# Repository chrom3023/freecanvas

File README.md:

# freecanvas #

         ___             ___                      
        | __| _ ___ ___ / __|__ _ _ ___ ____ _ ___
        | _| '_/ -_) -_) (__/ _` | ' \ V / _` (_-<
        |_||_| \___\___|\___\__,_|_||_\_/\__,_/__/

FreeCanvas is a development environment for experimental art based on Arduino.

## ChangeLog ##

-   FreeCanvas usa [versionamiento semántico](http://semver.org).  
-   Fuente de alimentación implementada.  
-   Fuente con salidas independientes.  
-   Actualizado el procesador a *ATMEGA2560*.  
-   Conexión USB a través de *FT232*.  
-   Incorporado conector AVRISP de seis pines.  
-   Añadidos múltiples indicadores de estado.  
-   Añadida la posibilidad de conectar varios maestros en cascada.

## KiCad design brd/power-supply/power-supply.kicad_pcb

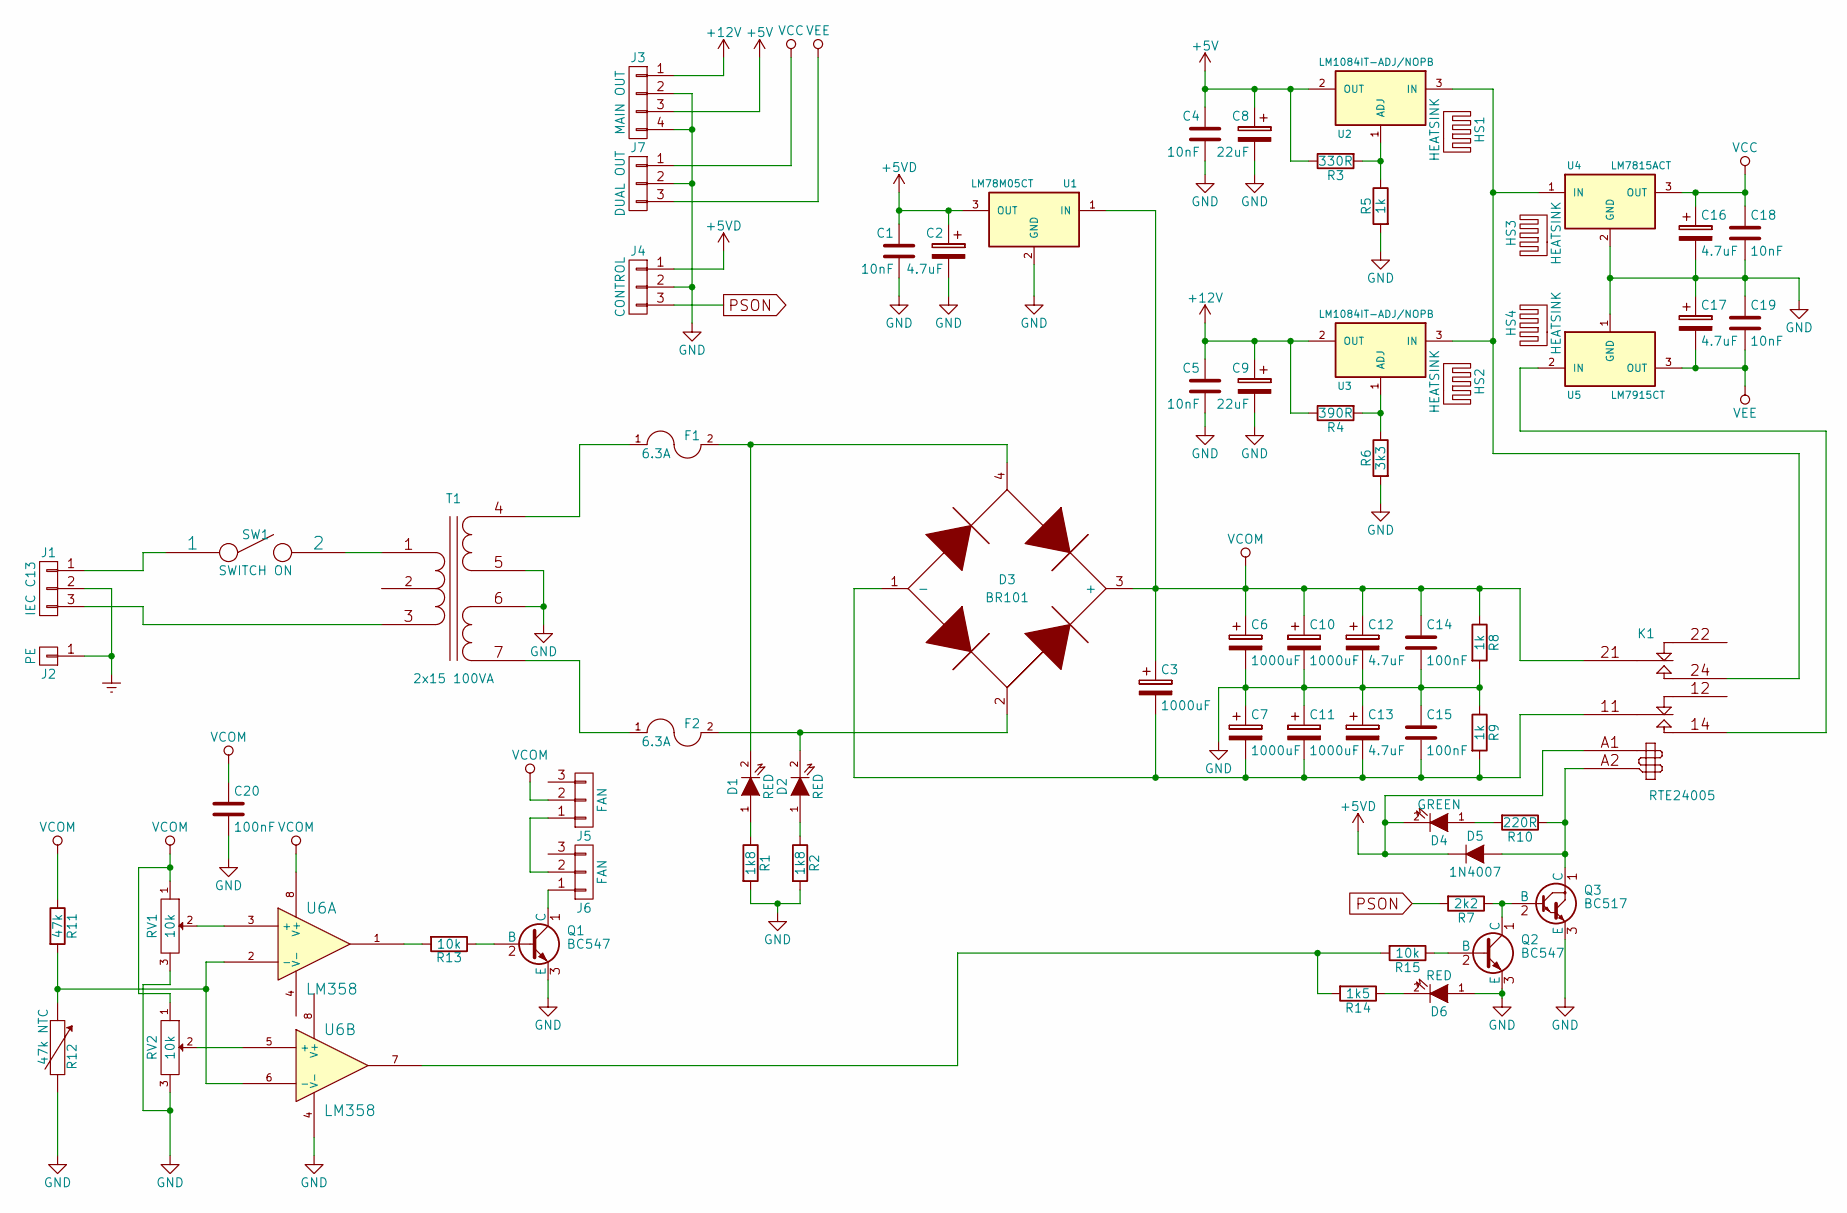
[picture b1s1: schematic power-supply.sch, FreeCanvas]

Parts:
C1, C4, C5, C18, C19: 10nF; C_Disc_D3_P2.5
C2, C12, C13, C16, C17: 4.7uF; C_Radial_D5_L11_P2
C3: 1000uF; C_Radial_D16_L25_P7.5
C6, C7, C10, C11: 1000uF; C_Radial_D12.5_L25_P5
C8, C9: 22uF; C_Radial_D5_L11_P2
C14, C15, C20: 100nF; C_Disc_D3_P2.5
D1, D2, D6: RED; LED-5MM
D3: BR101; BR-10
D4: GREEN; LED-5MM
D5: 1N4007; Diode_DO-41_SOD81_Horizontal_RM10
F1, F2: 6.3A; Fuseholder5x20-littelfuse646
HS1, HS2, HS3, HS4: HEATSINK; RA-T2X-xxE
J1: IEC C13; 703W-0053
J2: PE; douille_4mm
J3: MAIN OUT; 39880-0304
J4: CONTROL; 39880-0303
J5, J6: FAN; Socket_Strip_Straight_1x03
J7: DUAL OUT; 39880-0303
K1: RTE24005; Relay_DPDT_Schrack-RT2_RM5mm
Q1, Q2: BC547; TO-92_Inline_Wide
Q3: BC517; TO-92_Inline_Wide
R1, R2: 1k8; Resistor_Horizontal_RM15mm
R3: 330R; Resistor_Horizontal_RM10mm
R4: 390R; Resistor_Horizontal_RM10mm
R5: 1k; Resistor_Horizontal_RM10mm
R6: 3k3; Resistor_Horizontal_RM10mm
R7: 2k2; Resistor_Horizontal_RM10mm
R8, R9: 1k; Resistor_Horizontal_RM20mm
R10: 220R; Resistor_Horizontal_RM10mm
R11: 47k; Resistor_Horizontal_RM10mm
R12: 47k NTC; C_Disc_D3_P2.5
R13, R15: 10k; Resistor_Horizontal_RM10mm
R14: 1k5; Resistor_Horizontal_RM10mm
RV1, RV2: 10k; Potentiometer_Bourns_3296Y_3-8Zoll_Angular_ScrewUp
SW1: SWITCH ON; Carling-2M1-SP1-T2-B4-M6RE
T1: 2x15 100VA; VPT30-3330
U1: LM78M05CT; TO-220
U2, U3: LM1084IT-ADJ/NOPB; TO-220
U4: LM7815ACT; TO-220
U5: LM7915CT; TO-220
U6: LM358; DIP-8__300_ELL

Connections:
+5V: C4.1, C8.1, J3.3, R3.1, U2.2 (OUT)
+5VD: C1.1, C2.1, D4.2 (K), D5.1 (K), J4.1, K1.A1, U1.3 (OUT)
+12V: C5.1, C9.1, J3.1, R4.1, U3.2 (OUT)
Earth: J1.2, J2.1
GND: C1.2, C2.2, C4.2, C5.2, C6.2, C7.1, C8.2, C9.2, C10.2, C11.1, C12.2, C13.1, C14.2, C15.1, C16.2, C17.1, C18.2, C19.1, C20.2, D6.1 (A), J3.2, J3.4, J4.2, J7.2, Q1.3 (E), Q2.3 (E), Q3.3 (E), R1.2, R2.2, R5.2, R6.2, R8.2, R9.1, R12.2, RV1.3, RV2.3, T1.5 (OUT1B), T1.6 (OUT2A), U1.2 (GND), U4.2 (GND), U5.1 (GND), U6.4 (V-)
unnamed: C3.2, C7.2, C11.2, C13.2, C15.2, D3.1 (-), K1.11, R9.2
unnamed: D1.1 (A), R1.1
unnamed: D1.2 (K), D3.4, F1.2
unnamed: D2.1 (A), R2.1
unnamed: D2.2 (K), D3.2, F2.2
unnamed: D4.1 (A), R10.2
unnamed: D5.2 (A), K1.A2, Q3.1 (C), R10.1
unnamed: D6.2 (K), R14.1
unnamed: F1.1, T1.4 (OUT1A)
unnamed: F2.1, T1.7 (OUT2B)
unnamed: J1.1, SW1.1
unnamed: J1.3, T1.3 (IN-)
unnamed: J5.1, J6.2
unnamed: J6.1, Q1.1 (C)
unnamed: K1.14, U5.2 (IN)
unnamed: K1.24, U2.3 (IN), U3.3 (IN), U4.1 (IN)
unnamed: Q1.2 (B), R13.1
unnamed: Q2.1 (C), Q3.2 (B), R7.1
unnamed: Q2.2 (B), R15.1
unnamed: R3.2, R5.1, U2.1 (ADJ)
unnamed: R4.2, R6.1, U3.1 (ADJ)
unnamed: R11.2, R12.1, U6.2 (-), U6.6 (-)
unnamed: R13.2, U6.1
unnamed: R14.2, R15.2, U6.7
unnamed: RV1.2, U6.3 (+)
unnamed: RV2.2, U6.5 (+)
unnamed: SW1.2, T1.1 (IN+)
PSON: J4.3, R7.2
VCC: C16.1, C18.1, J7.1, U4.3 (OUT)
VCOM: C3.1, C6.1, C10.1, C12.1, C14.1, C20.1, D3.3 (+), J5.2, K1.21, R8.1, R11.1, RV1.1, RV2.1, U1.1 (IN), U6.8 (V+)
VEE: C17.2, C19.2, J7.3, U5.3 (OUT)

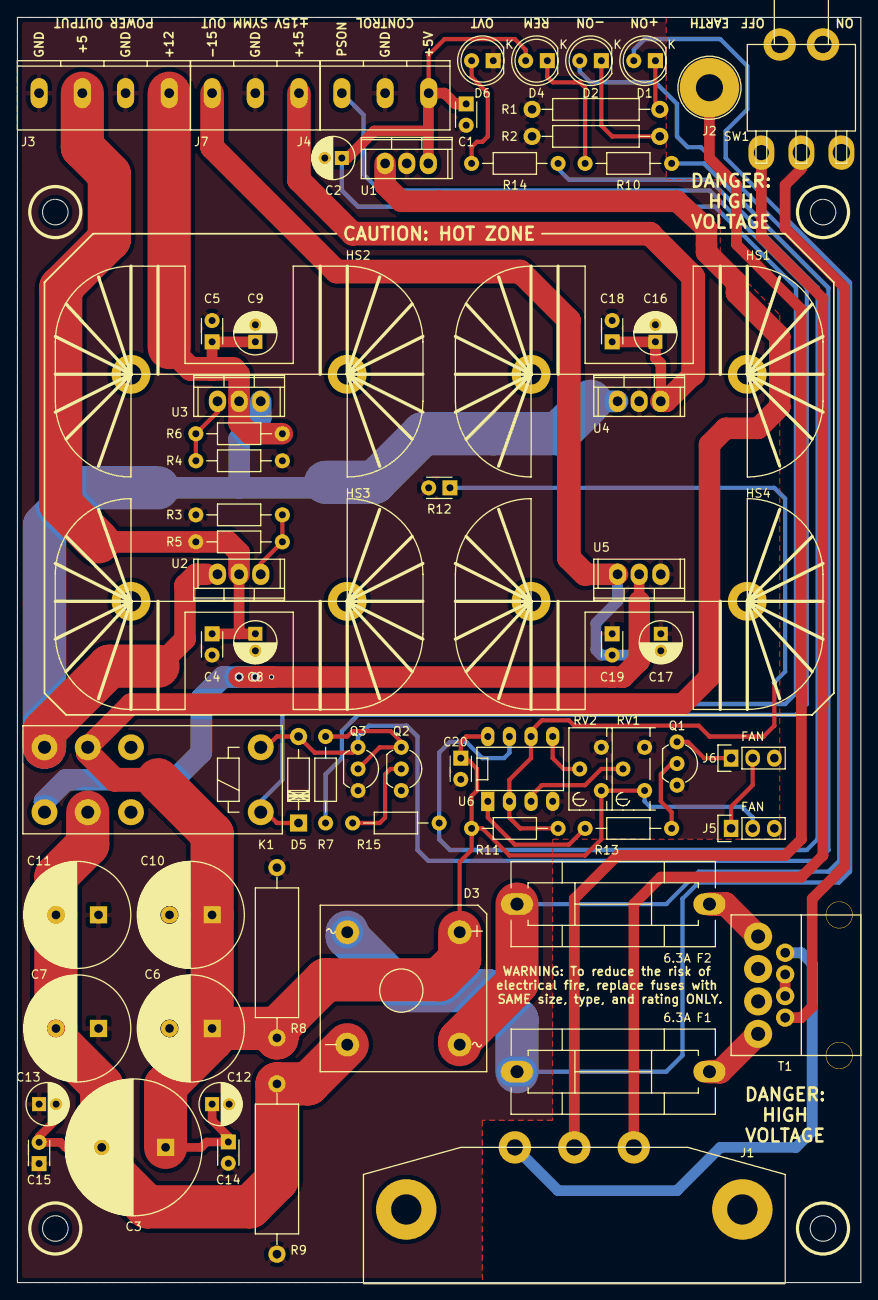
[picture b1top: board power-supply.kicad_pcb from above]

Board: 2 copper layers, 99.1 x 148.6 mm, 68 parts (0 on the bottom side), 36 nets.

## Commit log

2015-06-30 subida archivos
2015-08-18 version 1.1.2-rc añadido bom y referencias mouser en esquemático, corregido fallo de máscara en pcb y generado gerber

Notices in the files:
brd/power-supply/power-supply.kicad_pcb:
Under GPLv3 License
